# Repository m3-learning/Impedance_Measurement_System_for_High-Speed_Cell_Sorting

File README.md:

# Impedance_Measurement_System_for_High-Speed_Cell_Sorting

This impedance measurement PCB can be mounted on a National Instruments PXI System with a PXI-5412 arbitrary waveform generator and a PXIe-5122 Oscilloscope or similar modules. The voltage across R<sub>ref</sub> and the entire circuit can be used to calculate impedance with the 
<a href="https://assets.testequity.com/te1/Documents/pdf/impedance-measurement-handbook.pdf#page=23" target="_blank">I-V method</a>
 according to the following equation.

The Inventor part "spacer1" can be used to offset the SMB female socket.

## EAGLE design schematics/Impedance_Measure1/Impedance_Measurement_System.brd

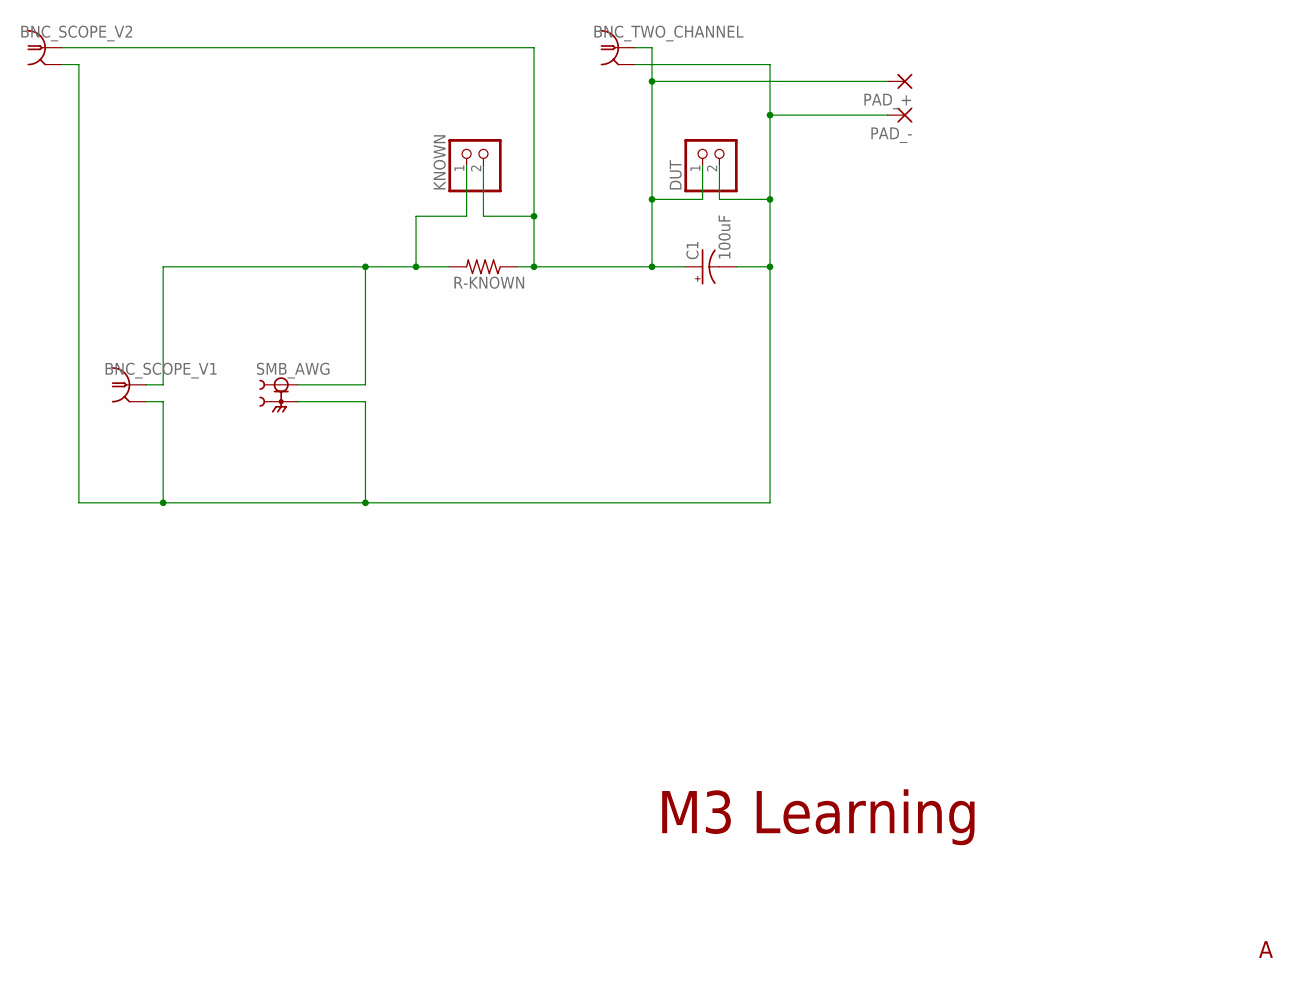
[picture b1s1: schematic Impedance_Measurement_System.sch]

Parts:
BNC_SCOPE_V1, BNC_SCOPE_V2: 112404
BNC_TWO_CHANNEL: 112404
C1: 100uF; CPOL-RADIAL-2.5MM-5MM
DUT: PINHD-1X2; 1X02
KNOWN: PINHD-1X2; 1X02
PAD_+: SMD5; SMD2,54-5,08
PAD_-: SMD5; SMD2,54-5,08
R-KNOWN: 10K; 0204/7
SMB_AWG: CONSMB006-G; LINX_CONSMB006-G

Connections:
unnamed: BNC_SCOPE_V1.1, KNOWN.1, R-KNOWN.2, SMB_AWG.1
unnamed: BNC_SCOPE_V1.2, BNC_SCOPE_V1.3 (2), BNC_SCOPE_V1.4 (2), BNC_SCOPE_V1.5 (2), BNC_SCOPE_V2.2, BNC_SCOPE_V2.3 (2), BNC_SCOPE_V2.4 (2), BNC_SCOPE_V2.5 (2), BNC_TWO_CHANNEL.2, BNC_TWO_CHANNEL.3 (2), BNC_TWO_CHANNEL.4 (2), BNC_TWO_CHANNEL.5 (2), C1.2 (-), DUT.2, PAD_-.1, SMB_AWG.G1 (2), SMB_AWG.G2 (2), SMB_AWG.G3 (2), SMB_AWG.G4 (2)
unnamed: BNC_SCOPE_V2.1, BNC_TWO_CHANNEL.1, C1.1 (+), DUT.1, KNOWN.2, PAD_+.1, R-KNOWN.1

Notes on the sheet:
M3 Learning

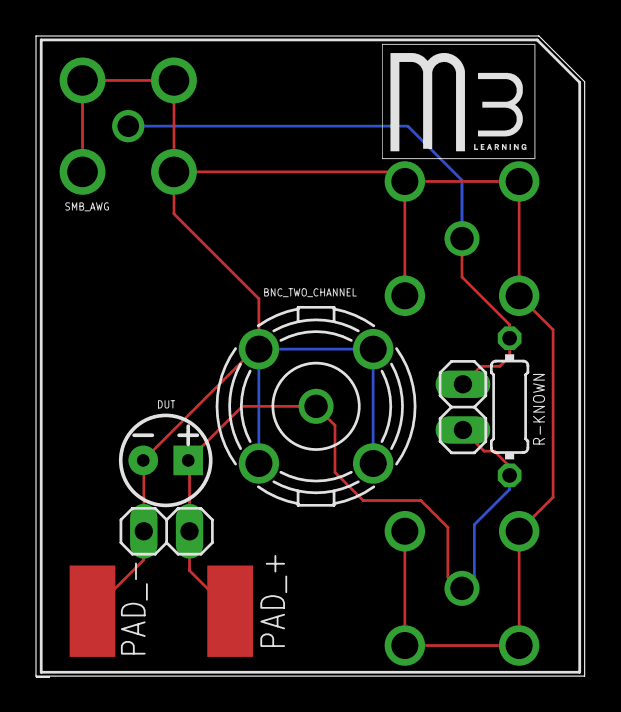
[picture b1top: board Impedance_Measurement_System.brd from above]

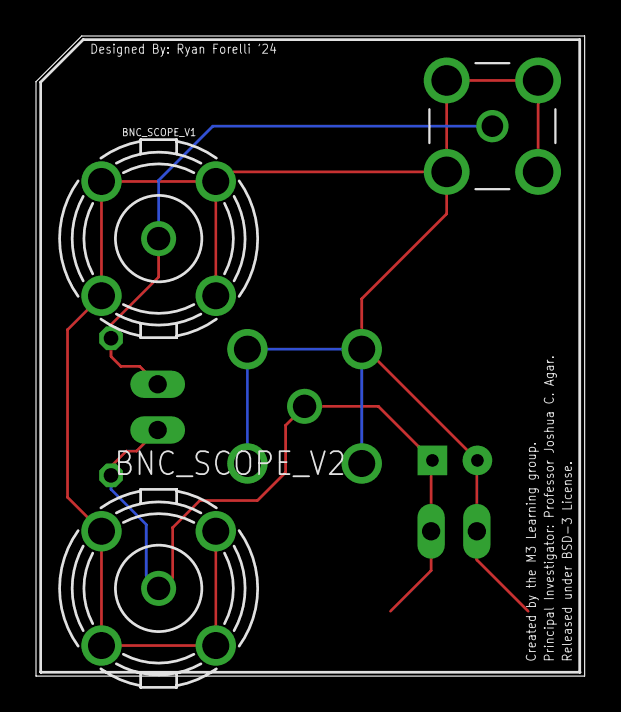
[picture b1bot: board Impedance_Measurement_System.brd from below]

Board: 2 copper layers, 30.5 x 35.6 mm, 10 parts (3 on the bottom side), 3 nets.

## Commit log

2021-07-04 schematics
2021-07-04 renders
2021-07-04 readme
2021-07-04 render
2021-07-04 schematic
2021-07-04 cad files

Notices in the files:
schematics/Impedance_Measure1/Impedance_Measurement_System.brd:
Released under BSD-3 License.
parts and their libraries:
SparkFun-Capacitors: Licensing: Creative Commons ShareAlike 4.0 International - https://creativecommons.org/licenses/by-sa/4.0
